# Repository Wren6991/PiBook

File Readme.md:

PiBook
======

Mini Raspberry Pi Compute Module-based laptop.

Unless stated otherwise (e.g. the contents of datasheets/) the contents of this repository is distributed under the revised BSD licence; see LICENSE.txt.

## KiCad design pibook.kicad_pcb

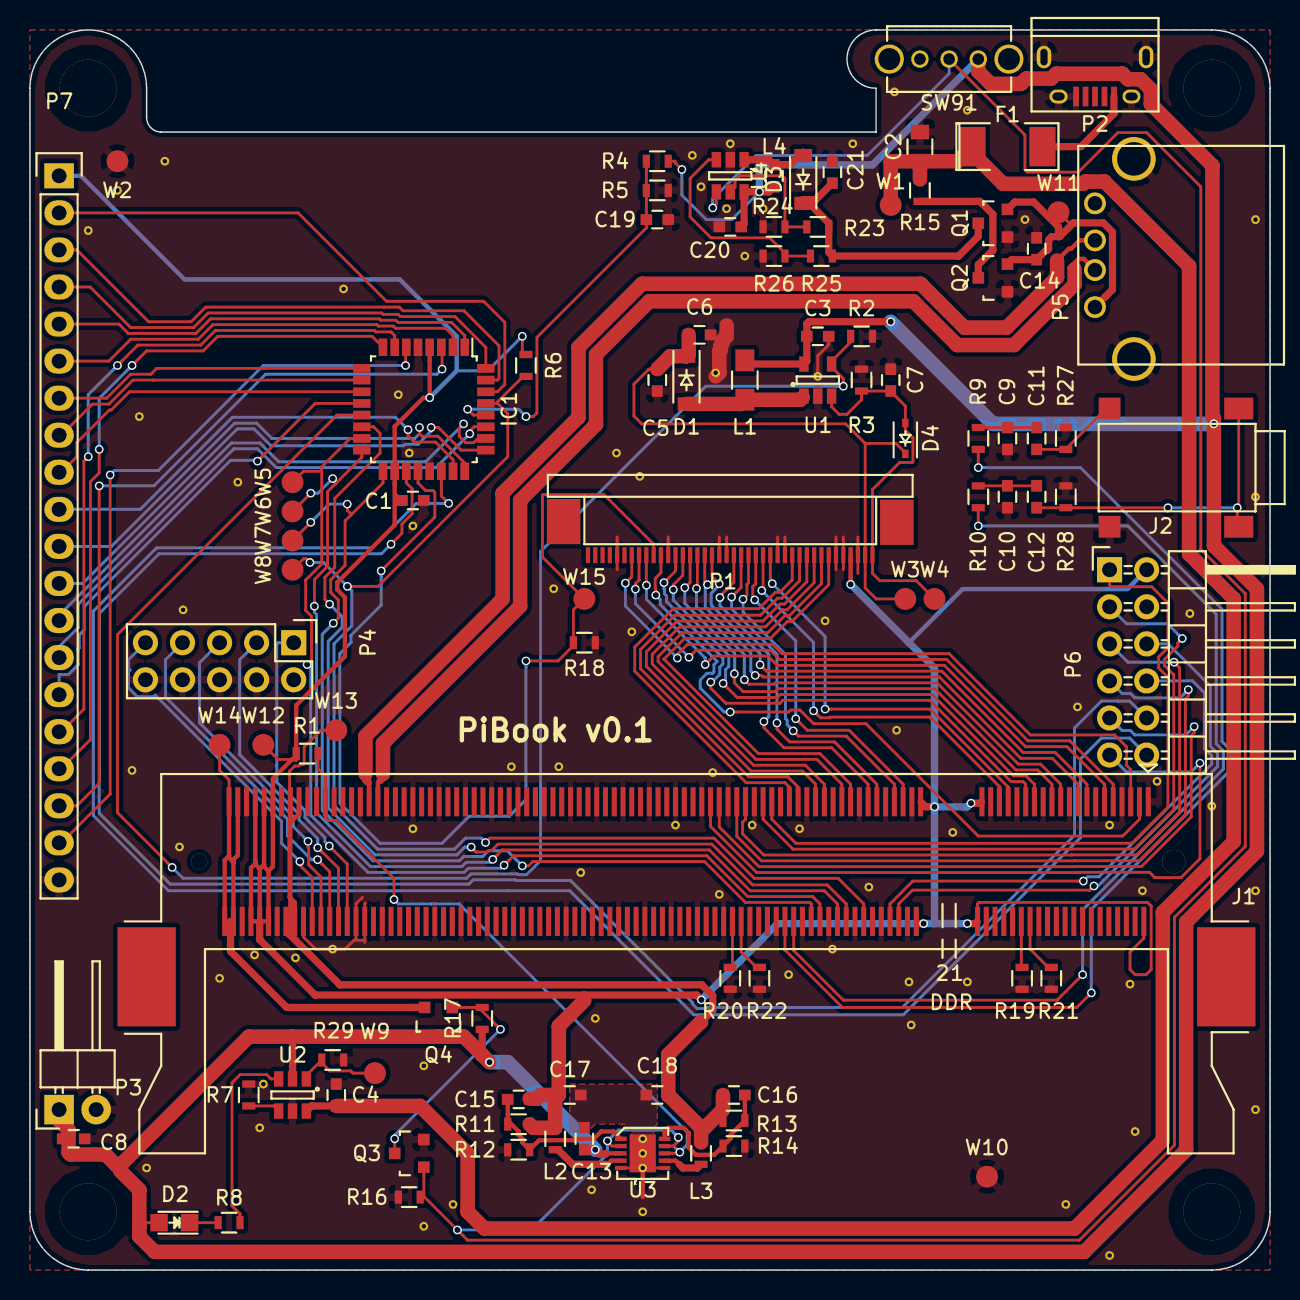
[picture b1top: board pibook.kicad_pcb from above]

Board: 2 copper layers, 85.0 x 85.0 mm, 98 parts (0 on the bottom side), 103 nets.

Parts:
C1, C4, C5, C6, C7, C8, C11, C12, C20, C21: 1u; C_0603
C2: 22u; C_0805
C3: 4.7u; C_0603
C9, C10: 82n; C_0603
C13, C14, C17, C18: 10u; C_0603
C15, C16: 18p; C_0603
C19: 100n; C_0603
D1, D3: MBR0540T3G; SOD-123
D2: LED; LED_0805
D4: MM32Z24VT1G; SOD-323
F1: 2A; SMD-2010_Pol
IC1: ATTINY48-A; LQFP-32_7x7mm_Pitch0.8mm
J1: ComputeModule; Socket_SODIMM_DDR1-2_TE_1612618
J2: TRS_JACK_3PIN; TRS_3_SMD
L1: 6.8u; R_0805_HandSoldering
L2, L3: 2.2u; R_0603
L4: 10u; C_0603
MH1, MH2, MH3, MH4: Mounting_Hole; Mounting_hole_M3.5
P1: CONN_01X40; FPC40_BOTTOM
P2: USB_OTG; USB_Micro-B
P3: CONN_01X02; Pin_Header_Angled_1x02
P4: CONN_02X05; Pin_Header_Straight_2x05
P5: USB_A
P6: CONN_02X06; Pin_Header_Angled_2x06
P7: CONN_01X20; Pin_Header_Straight_1x20
Q1, Q2, Q4: Si2323DS; SOT-23
Q3: BSS138P; SOT-23
R1, R2, R4, R5, R6, R12, R14, R16, R17, R18, R19, R20, R21, R22, R27, R28: 100k; R_0603
R3: 12; R_0603
R7: 680; R_0603
R8: R; R_0603
R9, R10: 100; R_0603
R11: 450k; R_0603
R13: 200k; R_0603
R15: 0; R_0603
R23: 47k; R_0603
R24, R26, R29: 10k; R_0603
R25: 40k; R_0603
SW91: SPST; SPDT_SLIDE_SWITCH
TP1: Tie_point; tiepoint-0.3
U1: FAN5333; SOT-23-5
U2: BQ21040; SOT-23-6
U3: NCP1532; UDFN-10
U4: MIC2619YD6; SOT-23-6
W1: USB_VIN+; Measurement_Point_Round-SMD-Pad_Small
W2: USB_VIN-; Measurement_Point_Round-SMD-Pad_Small
W3: BACKL_A; Measurement_Point_Round-SMD-Pad_Small
W4: BACKL_K; Measurement_Point_Round-SMD-Pad_Small
W5, W6, W7, W8, W15: TEST_1P; Measurement_Point_Round-SMD-Pad_Small
W9: TS; Measurement_Point_Round-SMD-Pad_Small
W10: GND; Measurement_Point_Round-SMD-Pad_Small
W11: VUSB_OUT; Measurement_Point_Round-SMD-Pad_Small
W12: +3V3; Measurement_Point_Round-SMD-Pad_Small
W13: +1V8; Measurement_Point_Round-SMD-Pad_Small
W14: CM_VBAT; Measurement_Point_Round-SMD-Pad_Small

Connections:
+1V8: C16.1, C18.1, J1.183, J1.184, J1.185, J1.186, L3.2, R13.1, W13.1
+3V3: C1.1, C15.1, C17.1, IC1.4, IC1.18, J1.2, J1.39, J1.40, J1.41, J1.42, J1.189, J1.190, J1.191, J1.192, J1.193, J1.194, L2.2, P1.4, P6.2, P7.1, R1.1, R6.1, R11.1, W12.1
+5V: C21.1, D3.1, Q1.3, R23.1, R25.1
+BATT: C3.1, C8.1, C13.1, C20.1, D2.2, L1.1, L4.1, P3.1, Q4.3, R4.1, R17.1, SW91.1, U1.5, U2.2, U3.3, U4.6
+VUSB_IN: C2.1, C4.1, F1.1, R15.2, U2.6, W1.1
+VUSB_OUT: C14.1, P5.1, Q1.2, Q2.2, W11.1
/ANALOG0: IC1.19, P6.10
/ANALOG1: IC1.22, P6.12
/AUDIO_L_PWM: J1.70, R10.2
/AUDIO_R_PWM: J1.72, R9.2
/AVR_MISO: IC1.16, J1.60, W6.1
/AVR_MOSI: IC1.15, J1.64, W5.1
/AVR_SCK: IC1.17, J1.66, W7.1
/AVR_~CS: IC1.14, J1.58
/AVR_~RST: IC1.29, J1.54, R6.2, W8.1
/BACKL_A: C5.1, C6.1, D1.1, D4.1, P1.2, W3.1
/BACKL_K: C7.1, D4.2, P1.1, R3.1, U1.3, W4.1
/BACKL_PWM: IC1.13, R2.1, U1.4
/CM_RUN: J1.177, R1.2, U3.8
/CM_VBAT: J1.197, J1.198, J1.199, J1.200, Q4.2, W14.1
/KEY_C0: IC1.30, P7.2
/KEY_C1: IC1.31, P7.3
/KEY_C2: IC1.32, P7.4
/KEY_C3: IC1.1, P7.5
/KEY_C4: IC1.2, P7.6
/KEY_C5: IC1.9, P7.7
/KEY_C6: IC1.10, P7.8
/KEY_C7: IC1.11, P7.9
/KEY_C8: IC1.23, P7.10
/KEY_C9: IC1.24, P7.11
/KEY_C10: IC1.25, P7.12
/KEY_C11: IC1.26, P7.13
/KEY_R0: IC1.27, P7.14
/KEY_R1: IC1.12, P7.15
/KEY_R2: IC1.7, P7.16
/KEY_R3: IC1.8, P7.17
/KEY_R4: IC1.3, P7.18
/KEY_R5: IC1.6, P7.19
/LCD_B_2: J1.15, P1.23
/LCD_B_3: J1.17, P1.24
/LCD_B_4: J1.21, P1.25
/LCD_B_5: J1.23, P1.26
/LCD_B_6: J1.27, P1.27
/LCD_B_7: J1.29, P1.28
/LCD_CLK: J1.3, P1.30
/LCD_DEN: J1.5, P1.34
/LCD_DISP_ON: IC1.20, P1.31, R18.1, W15.1
/LCD_G_2: J1.33, P1.15
/LCD_G_3: J1.35, P1.16
/LCD_G_4: J1.45, P1.17
/LCD_G_5: J1.47, P1.18
/LCD_G_6: J1.51, P1.19
/LCD_G_7: J1.53, P1.20
/LCD_HSYNC: J1.11, P1.32
/LCD_R_2: J1.57, P1.7
/LCD_R_3: J1.59, P1.8
/LCD_R_4: J1.63, P1.9
/LCD_R_5: J1.65, P1.10
/LCD_R_6: J1.69, P1.11
/LCD_R_7: J1.71, P1.12
/LCD_VSYNC: J1.9, P1.33
/PWR_ENABLE: Q3.1, R16.1, SW91.2, U3.2, U3.9, U4.4
/UART_RX: J1.48, P6.8
/UART_TX: J1.46, P6.6
/USB_D+: J1.165, P5.2
/USB_D-: J1.167, P5.3
/USER_IO_0: J1.75, P6.1
/USER_IO_1: J1.77, P6.3
/USER_IO_2: J1.81, P6.5
/USER_IO_3: J1.83, P6.7
/USER_IO_4: J1.87, P6.9
/USER_IO_5: J1.89, P6.11
/VC_TCK: J1.180, P4.9
/VC_TDI: J1.174, P4.3
/VC_TDO: J1.178, P4.5
/VC_TMS: J1.176, P4.7
/VC_TRST_N: J1.172, P4.1
GND: C1.2, C2.2, C3.2, C4.2, C5.2, C6.2, C7.2, C8.2, C9.2, C10.2, C14.2, C19.2, C20.2, C21.2, IC1.5, IC1.21, J1.1, J1.7, J1.13, J1.19, J1.25, J1.26, J1.31, J1.32, J1.37, J1.38, J1.43, J1.44, J1.49, J1.50, J1.55, J1.56, J1.61, J1.62, J1.67, J1.68, J1.73, J1.74, J1.79, J1.80, J1.85, J1.86, J1.91, J1.92, J1.97, J1.98, J1.103, J1.104, J1.109, J1.110, J1.115, J1.116, J1.121, J1.122, J1.127, J1.133, J1.134, J1.139, J1.140, J1.145, J1.146, J1.151, J1.152, J1.157, J1.163, J1.164, J1.168, J1.169, J1.170, J1.181, J1.182, J1.187, J1.188, J1.195, J1.196, J2.2, P1.3, P1.5, P1.6, P1.13, P1.14, P1.21, P1.22, P1.29, P1.36, P2.5, P2.6, P3.2, P4.2, P4.4, P4.6, P4.8, P4.10, P5.4, P5.5, P6.4, P7.20, Q1.1, Q2.1, Q3.2, R2.2, R3.2, R5.2, R7.1, R12.2, R14.2, R16.2, R18.2, R19.2, R20.2, R21.2, R22.2, R24.2, R26.2, R27.2, R28.2, R29.1, TP1.2, U1.2, U2.5, U4.2, W2.1, W10.1
GNDPWR: C13.2, C17.2, C18.2, TP1.1, U3.5, U3.6
unnamed: C10.1, C12.1, R10.1
unnamed: C9.1, C11.1, R9.1
unnamed: C11.2, J2.3, R27.1
unnamed: C12.2, J2.1, R28.1
unnamed: C15.2, R11.2, R12.1, U3.1
unnamed: C16.2, R13.2, R14.1, U3.10
unnamed: C19.1, IC1.28, R4.2, R5.1
unnamed: D1.2, L1.2, U1.1
unnamed: D2.1, R8.1
unnamed: D3.2, L4.2, U4.1
unnamed: F1.2, P2.1
unnamed: J1.28, R21.1
unnamed: J1.30, R19.1
unnamed: J1.82, R22.1
unnamed: J1.84, R20.1
unnamed: L2.1, U3.4
unnamed: L3.1, U3.7
unnamed: Q2.3, R15.1
unnamed: Q3.3, Q4.1, R17.2
unnamed: R7.2, U2.4
unnamed: R8.2, U2.3
unnamed: R23.2, R24.1, U4.5
unnamed: R25.2, R26.1, U4.3
unnamed: R29.2, U2.1, W9.1

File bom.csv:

Reference, Value, Footprint, Datasheet
R15,0,Resistors_SMD:R_0603,
R3,12,Resistors_SMD:R_0603,
R10,100,Resistors_SMD:R_0603,
R9,100,Resistors_SMD:R_0603,
R7,680,Resistors_SMD:R_0603,
W13,+1V8,Measurement_Points:Measurement_Point_Round-SMD-Pad_Small,
W12,+3V3,Measurement_Points:Measurement_Point_Round-SMD-Pad_Small,
R1,100k,Resistors_SMD:R_0603,
R12,100k,Resistors_SMD:R_0603,
R14,100k,Resistors_SMD:R_0603,
R16,100k,Resistors_SMD:R_0603,
R17,100k,Resistors_SMD:R_0603,
R18,100k,Resistors_SMD:R_0603,
R19,100k,Resistors_SMD:R_0603,
R2,100k,Resistors_SMD:R_0603,
R20,100k,Resistors_SMD:R_0603,
R21,100k,Resistors_SMD:R_0603,
R22,100k,Resistors_SMD:R_0603,
R27,100k,Resistors_SMD:R_0603,
R28,100k,Resistors_SMD:R_0603,
R4,100k,Resistors_SMD:R_0603,
R5,100k,Resistors_SMD:R_0603,
R6,100k,Resistors_SMD:R_0603,
C19,100n,Capacitors_SMD:C_0603,
R24,10k,Resistors_SMD:R_0603,
R26,10k,Resistors_SMD:R_0603,
R29,10k,Resistors_SMD:R_0603,
C13,10u,Capacitors_SMD:C_0603,
C14,10u,Capacitors_SMD:C_0603,
C17,10u,Capacitors_SMD:C_0603,
C18,10u,Capacitors_SMD:C_0603,
L4,10u,Capacitors_SMD:C_0603,
C15,18p,Capacitors_SMD:C_0603,
C16,18p,Capacitors_SMD:C_0603,
C1,1u,Capacitors_SMD:C_0603,
C11,1u,Capacitors_SMD:C_0603,
C12,1u,Capacitors_SMD:C_0603,
C20,1u,Capacitors_SMD:C_0603,
C21,1u,Capacitors_SMD:C_0603,
C4,1u,Capacitors_SMD:C_0603,
C5,1u,Capacitors_SMD:C_0603,
C6,1u,Capacitors_SMD:C_0603,
C7,1u,Capacitors_SMD:C_0603,
C8,1u,Capacitors_SMD:C_0603,
L2,2.2u,Resistors_SMD:R_0603,
L3,2.2u,Resistors_SMD:R_0603,
R13,200k,Resistors_SMD:R_0603,
C2,22u,Capacitors_SMD:C_0805,
F1,2A,SMD_Packages:SMD-2010_Pol,
C3,4.7u,Capacitors_SMD:C_0603,
R25,40k,Resistors_SMD:R_0603,
R11,450k,Resistors_SMD:R_0603,
R23,47k,Resistors_SMD:R_0603,
L1,6.8u,Resistors_SMD:R_0805_HandSoldering,
C10,82n,Capacitors_SMD:C_0603,
C9,82n,Capacitors_SMD:C_0603,
IC1,ATTINY48-A,Housings_QFP:LQFP-32_7x7mm_Pitch0.8mm,
W3,BACKL_A,Measurement_Points:Measurement_Point_Round-SMD-Pad_Small,
W4,BACKL_K,Measurement_Points:Measurement_Point_Round-SMD-Pad_Small,
U2,BQ21040,TO_SOT_Packages_SMD:SOT-23-6,
Q3,BSS138P,TO_SOT_Packages_SMD:SOT-23,
W14,CM_VBAT,Measurement_Points:Measurement_Point_Round-SMD-Pad_Small,
J1,ComputeModule,Sockets:Socket_SODIMM_DDR1-2_TE_1612618,DOCUMENTATION
P3,CONN_01X02,Pin_Headers:Pin_Header_Angled_1x02,
P7,CONN_01X20,Pin_Headers:Pin_Header_Straight_1x20,
P1,CONN_01X40,ComputeModule:FPC40_BOTTOM,
P4,CONN_02X05,Pin_Headers:Pin_Header_Straight_2x05,
P6,CONN_02X06,Pin_Headers:Pin_Header_Angled_2x06,
U1,FAN5333,TO_SOT_Packages_SMD:SOT-23-5,
W10,GND,Measurement_Points:Measurement_Point_Round-SMD-Pad_Small,
D2,LED,LEDs:LED_0805,
D1,MBR0540T3G,Diodes_SMD:SOD-123,
D3,MBR0540T3G,Diodes_SMD:SOD-123,
U4,MIC2619YD6,TO_SOT_Packages_SMD:SOT-23-6,
D4,MM32Z24VT1G,Diodes_SMD:SOD-323,
MH1,Mounting_Hole,ComputeModule:Mounting_hole_M3.5,
MH2,Mounting_Hole,ComputeModule:Mounting_hole_M3.5,
MH3,Mounting_Hole,ComputeModule:Mounting_hole_M3.5,
MH4,Mounting_Hole,ComputeModule:Mounting_hole_M3.5,
U3,NCP1532,ComputeModule:UDFN-10,
R8,R,Resistors_SMD:R_0603,
Q1,Si2323DS,TO_SOT_Packages_SMD:SOT-23,
Q2,Si2323DS,TO_SOT_Packages_SMD:SOT-23,
Q4,Si2323DS,TO_SOT_Packages_SMD:SOT-23,
SW91,SPST,ComputeModule:SPDT_SLIDE_SWITCH,
W15,TEST_1P,Measurement_Points:Measurement_Point_Round-SMD-Pad_Small,
W5,TEST_1P,Measurement_Points:Measurement_Point_Round-SMD-Pad_Small,
W6,TEST_1P,Measurement_Points:Measurement_Point_Round-SMD-Pad_Small,
W7,TEST_1P,Measurement_Points:Measurement_Point_Round-SMD-Pad_Small,
W8,TEST_1P,Measurement_Points:Measurement_Point_Round-SMD-Pad_Small,
TP1,Tie_point,,
J2,TRS_JACK_3PIN,ComputeModule:TRS_3_SMD,
W9,TS,Measurement_Points:Measurement_Point_Round-SMD-Pad_Small,
P5,USB_A,Connect:USB_A,
P2,USB_OTG,Connect:USB_Micro-B,
W2,USB_VIN-,Measurement_Points:Measurement_Point_Round-SMD-Pad_Small,
W1,USB_VIN+,Measurement_Points:Measurement_Point_Round-SMD-Pad_Small,
W11,VUSB_OUT,Measurement_Points:Measurement_Point_Round-SMD-Pad_Small,

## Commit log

2016-08-14 Added switch footprint
2016-08-14 Components all on PCB
2016-08-15 Routed DPI bus
2016-08-15 USB + some power routing
2016-08-15 New mechanical board layout
2016-08-16 Some more component placement
2016-08-16 All components placed
2016-08-16 Some more power routing
2016-08-16 AVR route out mostly done
2016-08-17 Rounded corners!
2016-08-23 Added USB boost converter to schematic
2016-08-23 5V + some extra routing
2016-08-23 All signals routed (still fails DRC)
2016-08-24 Corrected some DRC
2016-08-26 Working on new switchmode layout
2016-08-26 Routed the buck supply
2016-08-26 Improved backlight and 5v power layout; added bleed resistor to audio filter
2016-08-26 Improved USB impedance - 97 ohms diff vs 120
2016-08-26 fixed DRC, fixed component ref silkscreen
2016-08-27 Fixed up some things for production (putting NPTH in same drill file, tidied up some silk screen)
2016-08-27 Added gerbers/CAM files
2016-08-27 Fixed some DRCs
2016-08-27 Fixed DRCs and some grounding on the SODIMM
2016-08-27 Update schematic PDF, add BOM
2016-08-27 Adding readme, license
2016-08-30 Added some CAD images
2016-11-02 Corrected polarity of mosfet Q4 (switches CM_VBAT)
